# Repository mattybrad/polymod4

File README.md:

# PolyMod 4

A polyphonic digital synthesizer which can be patched like an analog modular synth.

Current setup is C++ code running on an Electrosmith Daisy board (with built-in DAC), on a PCB which includes potentiometers, buttons, LEDs, and circuitry to detect connections between output and input sockets.

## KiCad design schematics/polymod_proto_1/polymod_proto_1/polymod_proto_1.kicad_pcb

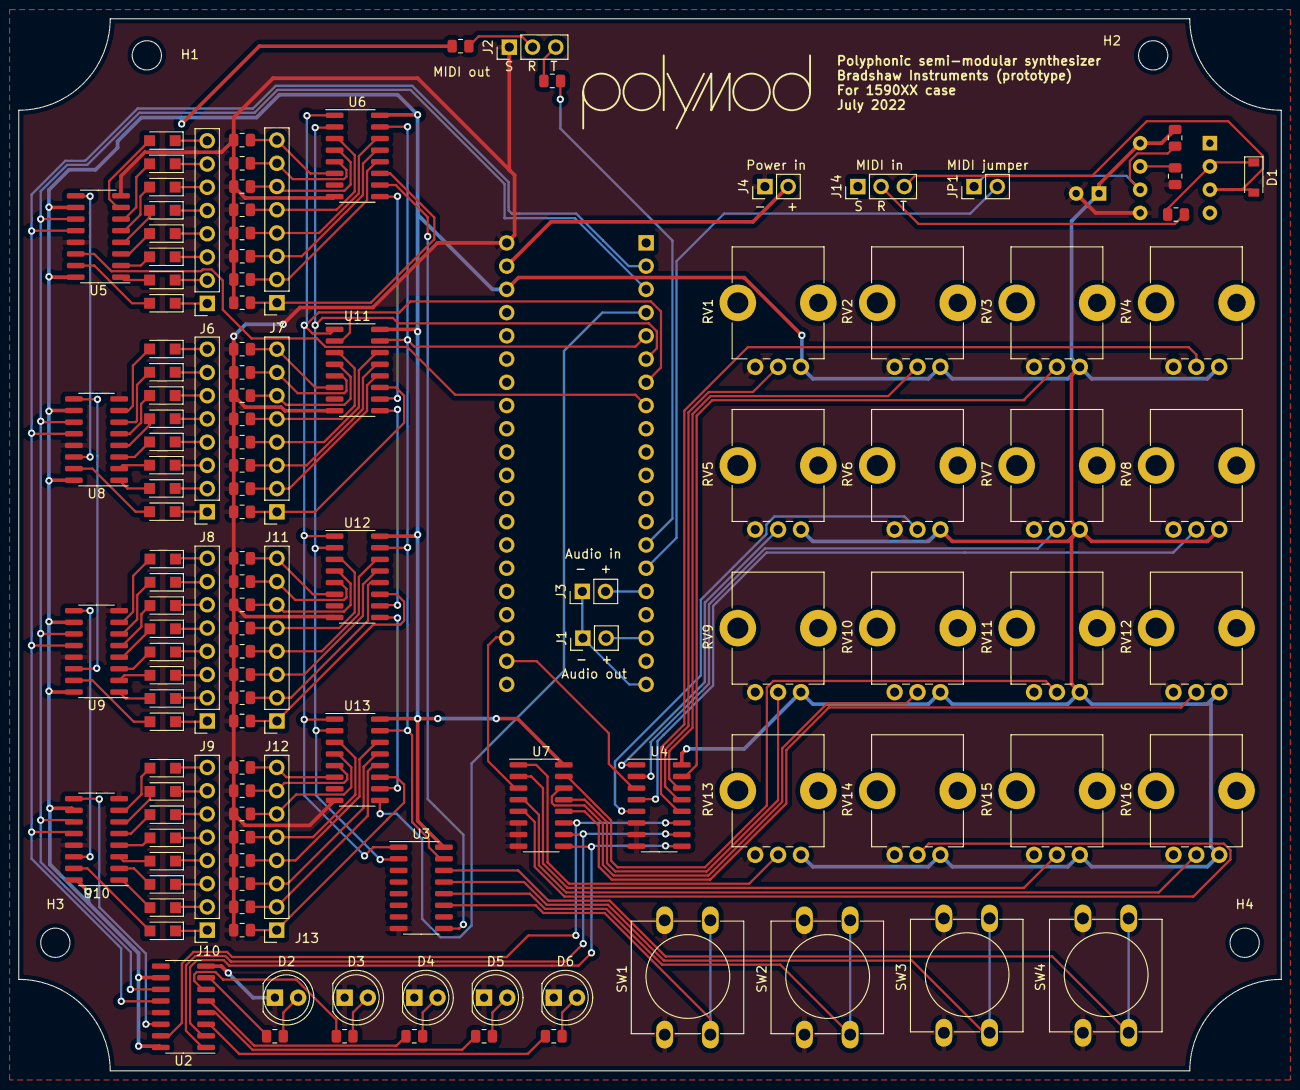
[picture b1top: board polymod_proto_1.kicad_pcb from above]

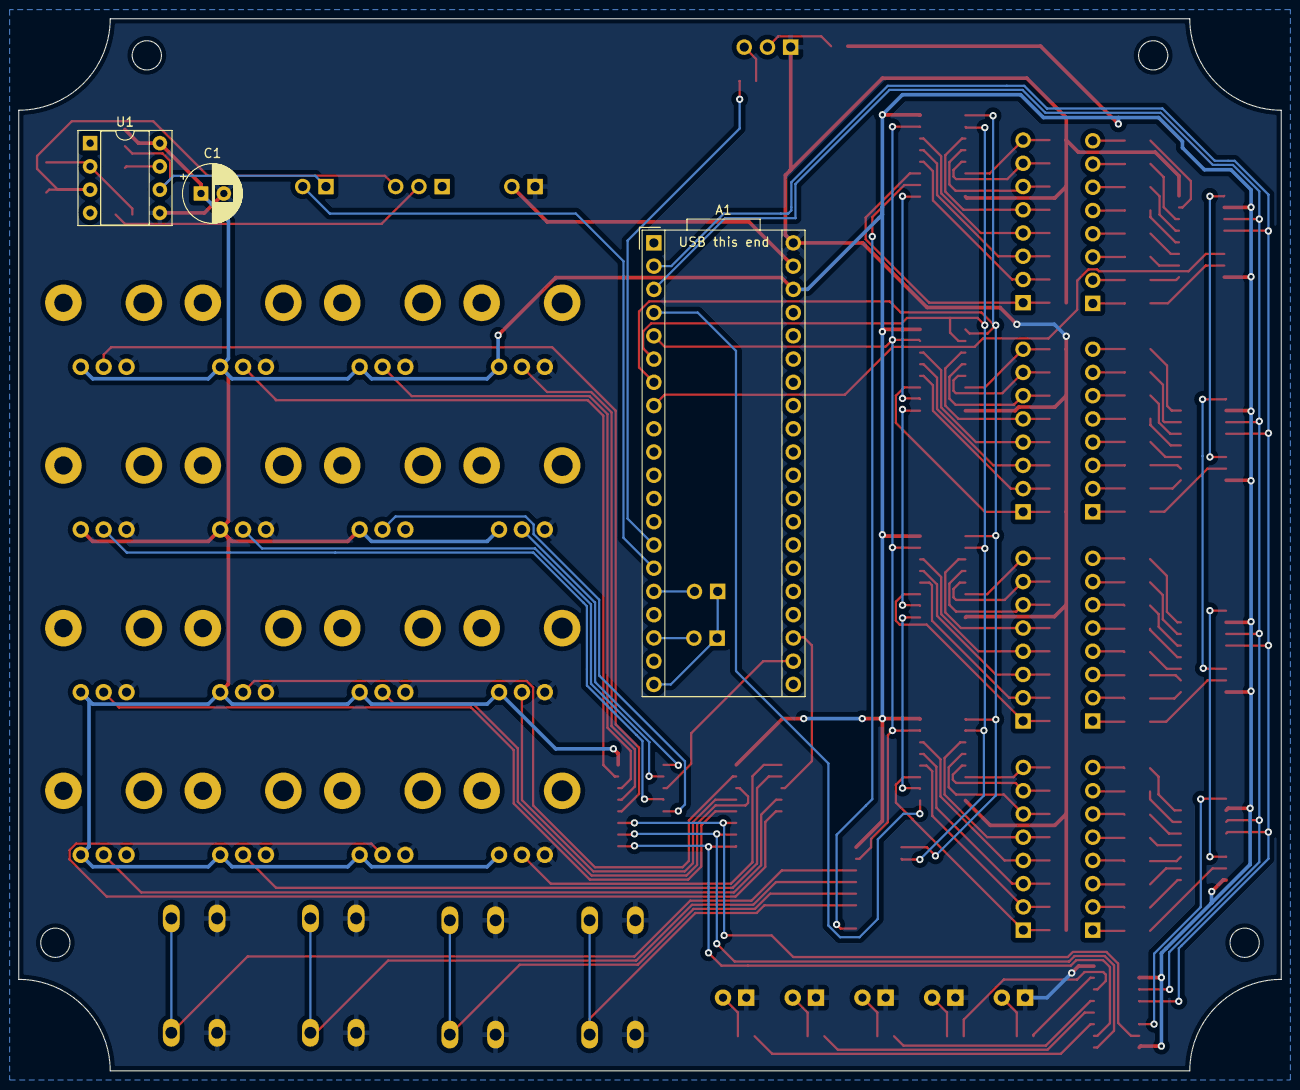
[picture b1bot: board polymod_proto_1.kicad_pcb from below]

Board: 2 copper layers, 138.0 x 115.0 mm, 133 parts (3 on the bottom side), 161 nets.

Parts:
A1: Device_Audio_Electrosmith_Daisy_Seed_Rev4; Device_Audio_Electrosmith_Daisy_Seed
C1: 470uF; CP_Radial_D6.3mm_P2.50mm
D1: 1N4148; D_SOD-123
D2, D3, D4, D5, D6: LED; LED_D5.0mm
D7, D8, D9, D10, D11, D12, D13, D14, D15, D16, D17, D18, D19, D20, D21, D22, D23, D24, D25, D26, D27, D28, D29, D30, D31, D32, D33, D34, D35, D36, D37, D38: 1N4148; Nexperia_CFP3_SOD-123W
H1, H2, H3, H4: MountingHole; MountingHole_3.2mm_M3
J1, J3: Conn_01x02_Male; PinHeader_1x02_P2.54mm_Vertical
J2, J14: Conn_01x03_Male; PinHeader_1x03_P2.54mm_Vertical
J4: Barrel_Jack; PinHeader_1x02_P2.54mm_Vertical
J6, J7, J8, J9, J10, J11, J12, J13: Conn_01x08_Male; PinSocket_1x08_P2.54mm_Vertical
JP1: Jumper_2_Open; PinHeader_1x02_P2.54mm_Vertical
R1, R4, R5: 220; R_0805_2012Metric
R2: 10k; R_0805_2012Metric
R3: 470; R_0805_2012Metric
R6, R7, R8, R9, R10: 680R; R_0805_2012Metric
R11, R12, R13, R14, R15, R16, R17, R18, R19, R20, R21, R22, R23, R24, R25, R26, R27, R28, R29, R30, R31, R32, R33, R34, R35, R36, R37, R38, R39, R40, R41, R42: 10K; R_0805_2012Metric
RV1, RV2, RV3, RV4, RV5, RV6, RV7, RV8, RV9, RV10, RV11, RV12, RV13, RV14, RV15, RV16: R_Potentiometer; Potentiometer_Alps_RK09K_Single_Vertical
SW1, SW2, SW3, SW4: SW_Push; SW_PUSH-12mm
U1: 6N138; DIP-8_W7.62mm_Socket
U2, U5, U8, U9, U10: 74HC595; SOIC-16_3.9x9.9mm_P1.27mm
U3, U6, U11, U12, U13: 74LS165; SOIC-16_3.9x9.9mm_P1.27mm
U4, U7: 4051; SOIC-16_3.9x9.9mm_P1.27mm

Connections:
4051_ADDRESS_A: U2.15 (QA), U4.11 (A), U7.11 (A)
4051_ADDRESS_B: U2.1 (QB), U4.10 (B), U7.10 (B)
4051_ADDRESS_C: U2.2 (QC), U4.9 (C), U7.9 (C)
/4051_1: A1.22 (ADC_INP10), U4.3 (X)
/4051_2: A1.23 (ADC_INP15), U7.3 (X)
/Input group 1/OUTPUT: U6.9 (Q7), U11.10 (DS)
/Input group 2/OUTPUT: U11.9 (Q7), U12.10 (DS)
/Input group 3/OUTPUT: U12.9 (Q7), U13.10 (DS)
/MIDI_IN: A1.15 (USART1_RX), JP1.2 (B)
/MIDI_OUT: A1.14 (USART1_TX), R5.2
/Output group 1/OUTPUT: U5.9 (QH'), U8.14 (SER)
/Output group 2/OUTPUT: U8.9 (QH'), U9.14 (SER)
/Output group 3/OUTPUT: U9.9 (QH'), U10.14 (SER)
/PATCHING_IN_DATA: A1.4 (SDMMC1_D1), U13.9 (Q7)
/PATCHING_OUT_DATA: A1.8 (SPI1_NSS), U5.14 (SER)
/UTIL_165: U3.9 (Q7), U6.10 (DS)
/UTIL_595: U2.14 (SER), U10.9 (QH')
/audio_in_tip: A1.16 (AUDIO_IN_L), J3.2
/audio_out_tip: A1.18 (AUDIO_OUT_L), J1.2
/midi_in_ring: J14.2, R1.2
/midi_in_tip: D1.2 (A), J14.3, U1.3 (C2)
/midi_out_ring: J2.2, R4.2
/midi_out_tip: J2.3, R5.1
GND: A1.40 (GND), C1.2, D2.1 (K), D3.1 (K), D4.1 (K), D5.1 (K), D6.1 (K), J2.1, J4.1, R2.1, R11.2, R12.2, R13.2, R14.2, R15.2, R16.2, R17.2, R18.2, R19.2, R20.2, R21.2, R22.2, R23.2, R24.2, R25.2, R26.2, R27.2, R28.2, R29.2, R30.2, R31.2, R32.2, R33.2, R34.2, R35.2, R36.2, R37.2, R38.2, R39.2, R40.2, R41.2, R42.2, RV1.3, RV2.3, RV3.3, RV4.3, RV5.3, RV6.3, RV7.3, RV8.3, RV9.3, RV10.3, RV11.3, RV12.3, RV13.3, RV14.3, RV15.3, RV16.3, SW1.1, SW2.1, SW3.1, SW4.1, U1.5 (GND), U2.8 (GND), U2.13 (~OE), U3.8 (GND), U4.6 (Inh), U4.7 (VEE), U4.8 (VSS), U5.8 (GND), U5.13 (~OE), U6.8 (GND), U7.6 (Inh), U7.7 (VEE), U7.8 (VSS), U8.8 (GND), U8.13 (~OE), U9.8 (GND), U9.13 (~OE), U10.8 (GND), U10.13 (~OE), U11.8 (GND), U12.8 (GND), U13.8 (GND)
GNDA: A1.20 (AGND), J1.1, J3.1
unnamed: A1.39 (VIN), J4.2
unnamed: D1.1 (K), R1.1, U1.2 (C1)
unnamed: D2.2 (A), R6.2
unnamed: D3.2 (A), R7.2
unnamed: D4.2 (A), R8.2
unnamed: D5.2 (A), R9.2
unnamed: D6.2 (A), R10.2
unnamed: D7.1 (K), J6.1
unnamed: D7.2 (A), U5.15 (QA)
unnamed: D8.1 (K), J6.2
unnamed: D8.2 (A), U5.1 (QB)
unnamed: D9.1 (K), J6.3
unnamed: D9.2 (A), U5.2 (QC)
unnamed: D10.1 (K), J6.4
unnamed: D10.2 (A), U5.3 (QD)
unnamed: D11.1 (K), J6.5
unnamed: D11.2 (A), U5.4 (QE)
unnamed: D12.1 (K), J6.6
unnamed: D12.2 (A), U5.5 (QF)
unnamed: D13.1 (K), J6.7
unnamed: D13.2 (A), U5.6 (QG)
unnamed: D14.1 (K), J6.8
unnamed: D14.2 (A), U5.7 (QH)
unnamed: D15.1 (K), J8.1
unnamed: D15.2 (A), U8.15 (QA)
unnamed: D16.1 (K), J8.2
unnamed: D16.2 (A), U8.1 (QB)
unnamed: D17.1 (K), J8.3
unnamed: D17.2 (A), U8.2 (QC)
unnamed: D18.1 (K), J8.4
unnamed: D18.2 (A), U8.3 (QD)
unnamed: D19.1 (K), J8.5
unnamed: D19.2 (A), U8.4 (QE)
unnamed: D20.1 (K), J8.6
unnamed: D20.2 (A), U8.5 (QF)
unnamed: D21.1 (K), J8.7
unnamed: D21.2 (A), U8.6 (QG)
unnamed: D22.1 (K), J8.8
unnamed: D22.2 (A), U8.7 (QH)
unnamed: D23.1 (K), J9.1
unnamed: D23.2 (A), U9.15 (QA)
unnamed: D24.1 (K), J9.2
unnamed: D24.2 (A), U9.1 (QB)
unnamed: D25.1 (K), J9.3
unnamed: D25.2 (A), U9.2 (QC)
unnamed: D26.1 (K), J9.4
unnamed: D26.2 (A), U9.3 (QD)
unnamed: D27.1 (K), J9.5
unnamed: D27.2 (A), U9.4 (QE)
unnamed: D28.1 (K), J9.6
unnamed: D28.2 (A), U9.5 (QF)
unnamed: D29.1 (K), J9.7
unnamed: D29.2 (A), U9.6 (QG)
unnamed: D30.1 (K), J9.8
unnamed: D30.2 (A), U9.7 (QH)
unnamed: D31.1 (K), J10.1
unnamed: D31.2 (A), U10.15 (QA)
unnamed: D32.1 (K), J10.2
unnamed: D32.2 (A), U10.1 (QB)
unnamed: D33.1 (K), J10.3
unnamed: D33.2 (A), U10.2 (QC)
unnamed: D34.1 (K), J10.4
unnamed: D34.2 (A), U10.3 (QD)
unnamed: D35.1 (K), J10.5
unnamed: D35.2 (A), U10.4 (QE)
unnamed: D36.1 (K), J10.6
unnamed: D36.2 (A), U10.5 (QF)
unnamed: D37.1 (K), J10.7
unnamed: D37.2 (A), U10.6 (QG)
unnamed: D38.1 (K), J10.8
unnamed: D38.2 (A), U10.7 (QH)
unnamed: J7.1, R17.1, U6.11 (D0)
unnamed: J7.2, R15.1, U6.12 (D1)
unnamed: J7.3, R13.1, U6.13 (D2)
unnamed: J7.4, R11.1, U6.14 (D3)
unnamed: J7.5, R18.1, U6.3 (D4)
unnamed: J7.6, R16.1, U6.4 (D5)
unnamed: J7.7, R14.1, U6.5 (D6)
unnamed: J7.8, R12.1, U6.6 (D7)
unnamed: J11.1, R25.1, U11.11 (D0)
unnamed: J11.2, R23.1, U11.12 (D1)
unnamed: J11.3, R21.1, U11.13 (D2)
unnamed: J11.4, R19.1, U11.14 (D3)
unnamed: J11.5, R26.1, U11.3 (D4)
unnamed: J11.6, R24.1, U11.4 (D5)
unnamed: J11.7, R22.1, U11.5 (D6)
unnamed: J11.8, R20.1, U11.6 (D7)
unnamed: J12.1, R33.1, U12.11 (D0)
unnamed: J12.2, R31.1, U12.12 (D1)
unnamed: J12.3, R29.1, U12.13 (D2)
unnamed: J12.4, R27.1, U12.14 (D3)
unnamed: J12.5, R34.1, U12.3 (D4)
unnamed: J12.6, R32.1, U12.4 (D5)
unnamed: J12.7, R30.1, U12.5 (D6)
unnamed: J12.8, R28.1, U12.6 (D7)
unnamed: J13.1, R41.1, U13.11 (D0)
unnamed: J13.2, R39.1, U13.12 (D1)
unnamed: J13.3, R37.1, U13.13 (D2)
unnamed: J13.4, R35.1, U13.14 (D3)
unnamed: J13.5, R42.1, U13.3 (D4)
unnamed: J13.6, R40.1, U13.4 (D5)
unnamed: J13.7, R38.1, U13.5 (D6)
unnamed: J13.8, R36.1, U13.6 (D7)
unnamed: JP1.1 (A), R3.2, U1.6 (VO2)
unnamed: R2.2, U1.7 (VO1)
unnamed: R6.1, U2.7 (QH)
unnamed: R7.1, U2.6 (QG)
unnamed: R8.1, U2.5 (QF)
unnamed: R9.1, U2.4 (QE)
unnamed: R10.1, U2.3 (QD)
unnamed: RV1.2, U4.13 (X0)
unnamed: RV2.2, U4.14 (X1)
unnamed: RV3.2, U4.15 (X2)
unnamed: RV4.2, U4.12 (X3)
unnamed: RV5.2, U4.1 (X4)
unnamed: RV6.2, U4.5 (X5)
unnamed: RV7.2, U4.2 (X6)
unnamed: RV8.2, U4.4 (X7)
unnamed: RV9.2, U7.13 (X0)
unnamed: RV10.2, U7.14 (X1)
unnamed: RV11.2, U7.15 (X2)
unnamed: RV12.2, U7.12 (X3)
unnamed: RV13.2, U7.1 (X4)
unnamed: RV14.2, U7.5 (X5)
unnamed: RV15.2, U7.2 (X6)
unnamed: RV16.2, U7.4 (X7)
unnamed: SW1.2, U3.11 (D0)
unnamed: SW2.2, U3.12 (D1)
unnamed: SW3.2, U3.13 (D2)
unnamed: SW4.2, U3.14 (D3)
PATCHING_IN_CE: A1.5 (SDMMC1_D0), U3.15 (~CE), U6.15 (~CE), U11.15 (~CE), U12.15 (~CE), U13.15 (~CE)
PATCHING_IN_CLOCK: A1.6 (SDMMC1_CMD), U3.2 (CP), U6.2 (CP), U11.2 (CP), U12.2 (CP), U13.2 (CP)
PATCHING_IN_LOAD: A1.7 (SDMMC1_CK), U3.1 (~PL), U6.1 (~PL), U11.1 (~PL), U12.1 (~PL), U13.1 (~PL)
PATCHING_OUT_CLOCK: A1.3 (SDMMC1_D2), U2.11 (SRCLK), U5.11 (SRCLK), U8.11 (SRCLK), U9.11 (SRCLK), U10.11 (SRCLK)
PATCHING_OUT_LATCH: A1.2 (SDMMC1_D3), U2.12 (RCLK), U5.12 (RCLK), U8.12 (RCLK), U9.12 (RCLK), U10.12 (RCLK)
VCC: A1.38 (3V3_D), C1.1, R3.1, R4.1, RV1.1, RV2.1, RV3.1, RV4.1, RV5.1, RV6.1, RV7.1, RV8.1, RV9.1, RV10.1, RV11.1, RV12.1, RV13.1, RV14.1, RV15.1, RV16.1, U1.8 (VCC), U2.10 (~SRCLR), U2.16 (VCC), U3.16 (VCC), U4.16 (VDD), U5.10 (~SRCLR), U5.16 (VCC), U6.16 (VCC), U7.16 (VDD), U8.10 (~SRCLR), U8.16 (VCC), U9.10 (~SRCLR), U9.16 (VCC), U10.10 (~SRCLR), U10.16 (VCC), U11.16 (VCC), U12.16 (VCC), U13.16 (VCC)

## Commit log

2021-10-07 starting patchbay schematic
2021-10-07 schematic progress
2021-10-10 first attempt at arduino patchbay library
2021-10-11 patchbay working pretty well
2021-10-11 updated patchbay schematic with diodes and pulldown resistors
2021-10-14 second 165 register working
2021-10-14 tidying up shift reg code
2021-10-15 patchbay code looks nice
2021-10-18 changed teensy pins for prototype, added 4 pots
2021-10-23 reorganising, bringing in code from polymod3
2021-10-25 fixed the stupid memory leak!
2021-10-25 2 VCOs with analog control
2021-10-25 mixer working nicely
2021-10-26 making a mess, sorting out recursive polyphonic things
2021-10-26 kinda working!
2021-10-26 i am bad at naming commits
2021-10-27 increased max polyphony from 4 to 16
2021-10-27 prevent crash on bad connection
2021-10-27 filter!
2021-10-28 mono connections now working
2021-10-28 can't figure out midi to fake CV conversion yet
2021-10-29 midi note on working nicely via usb!
2021-11-01 good start with midi
2021-11-01 midi gate
2021-11-02 ummm a bunch of things, mult, ADSR? general improvements...
2022-01-17 something is broken
2022-01-18 after several hours of annoyance, realised that one line was preventing audioconnections disconnecting properly
2022-01-18 little tweak
2022-01-19 oops worked on two computers and didn't push...
2022-01-21 planning pins for new prototype
2022-01-21 more pin stuff
2022-01-24 started kicad layout for first proper prototype
2022-01-26 oled stuff
2022-01-27 graphics and audio working off same I2C pins
2022-06-09 something
2022-06-10 better layout?
2022-06-15 proto panel looks nice
2022-06-15 playing around with electrosmith daisy boards, bit of a mess right now
2022-06-15 schematic is getting somewhere
2022-06-20 schematic nearly done
2022-06-20 pcb layout about to start
2022-06-20 layout going well
2022-07-07 oops forgot to commit
2022-07-07 components pretty much in place
2022-07-07 routing started
2022-07-08 routing is HARD
2022-07-10 better layout/routing
2022-07-10 ummm less sure this is working well but not awful
2022-07-11 about to restart routing again
2022-07-11 reposition things for more efficient routing
2022-07-11 really shouldn't be committing all these zip backups...
2022-07-12 mainly just ground routing now
2022-07-13 routed!
2022-07-13 no drc warnings
2022-07-13 added helpful notes
2022-07-13 maybe ready for fabrication!
2022-07-13 gerbers!
2022-07-18 added daisy submodule
2022-07-18 started writing patching code for daisy
2022-07-18 end of a very hot day
2022-07-18 just kinda messing about, trying to recreate teensy version on daisy
2022-07-20 cad stuff
2022-07-20 faffing with the case
2022-07-21 IT WORKSgit add --a!
2022-07-21 found the issue with analog inputs
2022-07-21 quick thought about reducing pin count
2022-07-22 stupid zips
2022-08-01 fixed issue with dodgy 4051 readings
2022-08-01 gitignore
2022-08-01 gitignore..?
2022-08-01 stupid gitignore
2022-08-01 clean up ignored files...
2022-08-01 okay done faffing with gitignore
2022-08-01 getting serious
2022-08-01 patching works! can read connections/disconnections
2022-08-01 stable input readings
2022-08-03 adding modules
2022-08-04 a sound! the patch cable made a sound!
2022-08-04 disconnection works! multiple VCOs work!
2022-08-04 removed serial dependency
2022-08-04 working through some things
2022-08-04 kinda redesigned all the classes in a rambling text file
2022-08-05 i don't understand pointers and i have made a mess
2022-08-08 a pause to learn about circular dependency
2022-08-08 yet more understanding of pointers etc
2022-08-08 fixing something
2022-08-08 fixing...
2022-08-08 wrote a lot of code, it won't work
2022-08-08 the shed is hot but the new code layout seems to work
2022-08-08 okay, the process of setting up modules/sockets is ugly, but it works well
2022-08-08 that'll do for today - great progress
2022-08-10 tidied up socket init nicely, and seems i can store socket pointers in module - win!
2022-08-11 pseudo sources working properly!
2022-08-11 why can't i fix the pin number ordering..?
2022-08-11 oops
2022-08-11 pseudo connections now working better
2022-08-11 logical pin numbers!
2022-08-11 rudimentary cpu monitoring
2022-08-12 i have made a mess
2022-08-12 more mess
2022-08-15 semi-drastic rewrite to tidy up the socket/connection system before attempting polyphony again
2022-08-15 POLYPHONYgit add --a!
2022-08-15 broke it in a rush
2022-08-17 lots of frustrating messing about today, maybe finally figuring out some issues
2022-08-17 polyphony stuck at max 2..?!
2022-08-18 aha! had some dodgy pointers, added a check
2022-08-18 re-added physical patching
2022-08-18 vco freq in works
2022-08-22 oops didn't commit
2022-08-22 midi working in test file
2022-08-22 midi seems to work
2022-08-22 largely good midi progress but error if lots of midi events at once..?
2022-08-24 just testing various things
2022-08-25 bodged the problem where filter crashed for certain frequency values
2022-08-25 VCA works
2022-08-25 envelope works, test connections handled better
2022-08-25 simple mult working
2022-08-25 white noise works, mixer works
2022-08-25 test synth voice works nicely
2022-08-25 reorganised modules, audio input working
2022-08-25 starting to add knobs
2022-08-25 added more analog controls
2022-08-25 just some notes
2022-09-02 testing qspi stuff
2023-05-09 long break
